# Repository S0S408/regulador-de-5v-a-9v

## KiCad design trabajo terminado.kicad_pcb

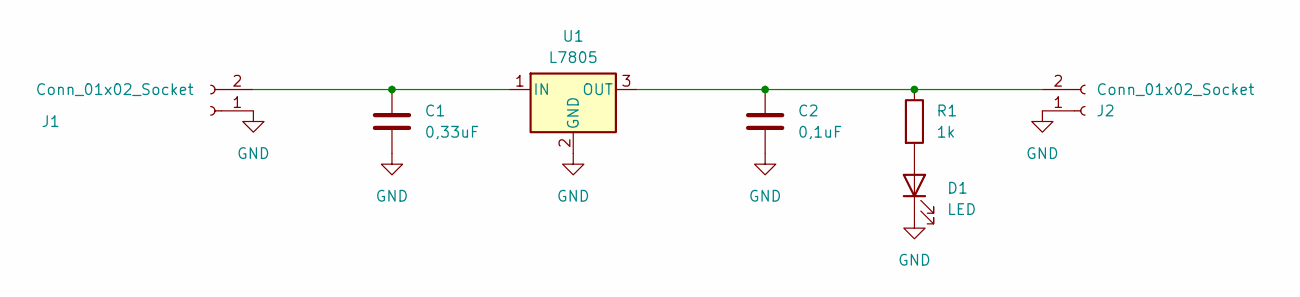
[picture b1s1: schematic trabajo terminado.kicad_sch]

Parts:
C1: 0,33uF; C_0805_2012Metric
C2: 0,1uF; C_0805_2012Metric
D1: LED; LED_1206_3216Metric
J1, J2: Conn_01x02_Socket; Molex_KK-254_AE-6410-02A_1x02_P2.54mm_Vertical
R1: 1k; R_0805_2012Metric
U1: L7805; TO-220-3_Vertical

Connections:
GND: C1.2, C2.2, D1.1 (K), J1.1, J2.1, U1.2 (GND)
unnamed: D1.2 (A), R1.2
unnamed: C1.1, J1.2, U1.1 (IN)
unnamed: C2.1, J2.2, R1.1, U1.3 (OUT)

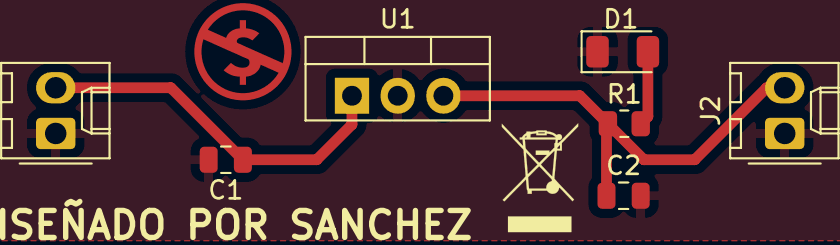
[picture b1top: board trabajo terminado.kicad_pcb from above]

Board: 2 copper layers, 7 parts (0 on the bottom side), 4 nets.

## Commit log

2024-07-12 esquematico y pcb de un regulador de tension de 5v a 9v
    COMPONENTES:
    1 l7805 (El L7805 es un regulador de voltaje que proporciona una salida estable de +5 voltios a partir de una entrada más alta de voltaje)
    2 condensadores electroliticos (Los condensadores electrolíticos se utilizan principalmente para filtrar voltaje, desacoplar señales, suavizar corrientes eléctricas y almacenar energía en circuitos e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
    1 resistencia de 1k (son componentes electrónicos que limitan la corriente eléctrica)
    2 conectores de 2 pines (permiten establecer una conexión eléctrica directa y sencilla entre dos componentes o dispositivos en circuitos electrónicos).
    LA RAZON DE ESTE PROYECTO
